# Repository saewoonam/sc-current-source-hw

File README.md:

# CAD file for supercables 8 channel current source

## Folder descriptions:
- 8ch_currentsource_jlc_v4:   KiCAD files of the elecronic circuit
- front_panel:  PCB design for the front panel of the enclosure
- back_panel:  PCB design for rthe back panel of the enclosure
- supercables-curernt-source-enclosure:  FreeCAD file and step files of the assembled box

## [Assembly Instructions](https://github.com/saewoonam/sc-current-source-hw/blob/main/Assembly_Instructions.md)

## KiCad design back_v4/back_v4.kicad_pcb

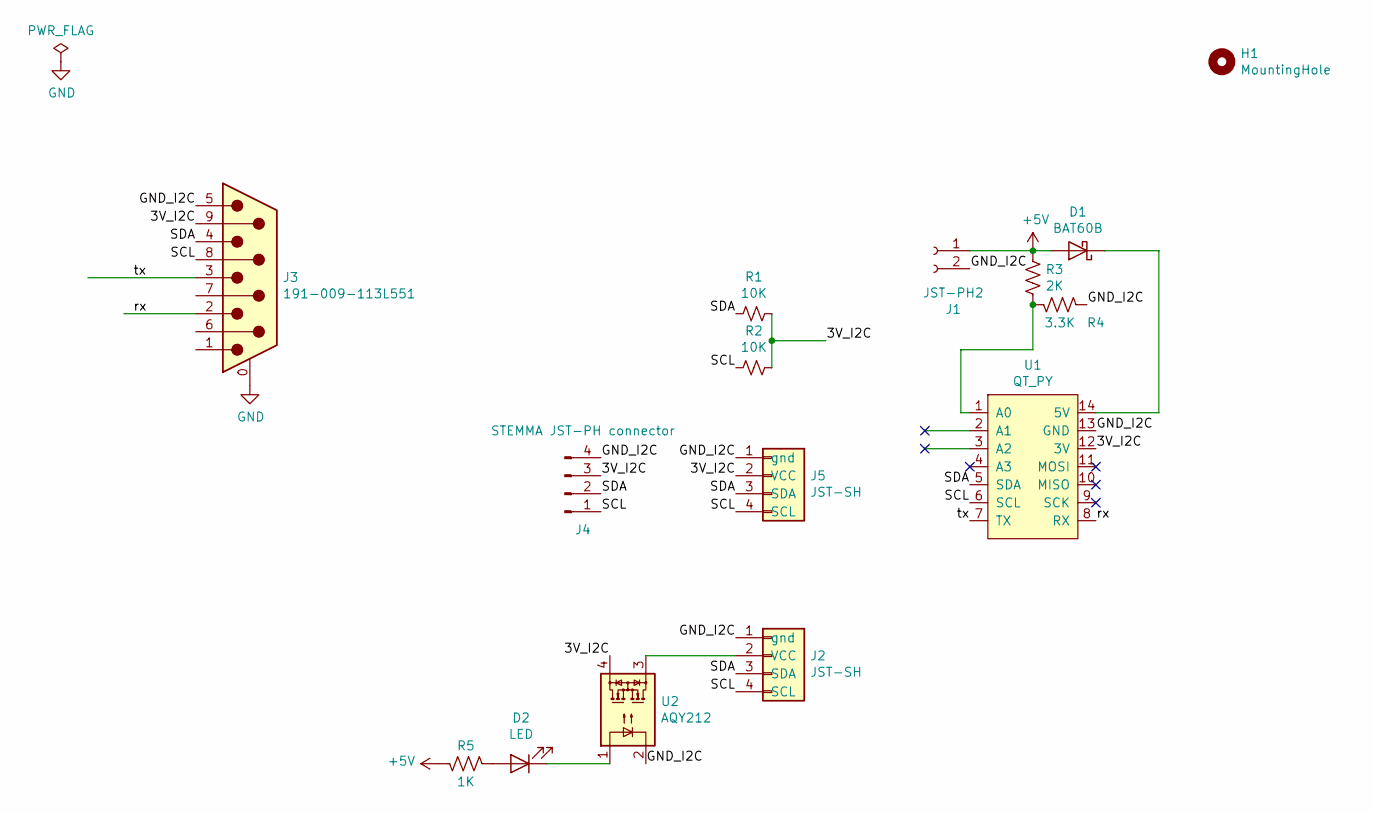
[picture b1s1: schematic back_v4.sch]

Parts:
D1: BAT60B; D_SOD-323; MPN BAT60B; LCSC C514095
D2: LED; LED_0603_1608Metric_Pad1.05x0.95mm_HandSolder; MPN KT-0603R; LCSC C2286
H1: MountingHole; MountingHole_8.4mm_PJ-066
J1: JST-PH2; JST_PH_B2B-PH-SM4-TB_1x02-1MP_P2.00mm_Vertical; MPN B2B-PH-SM4-TB(lf)(sn)
J2, J5: JST-SH; JST_SH_BM04B-SRSS-TB_1x04-1MP_P1.00mm_Vertical; MPN JST-SH-BM04B-SRSS-TB
J3: 191-009-113L551; DSUB-9_Male_Vertical_P2.77x2.84mm_MountingHoles; MPN 191-009-113L551
J4: STEMMA JST-PH connector; JST_PH_B4B-PH-SM4-TB_1x04-1MP_P2.00mm_Vertical; MPN B4B-PH-SM4-TB(lf)(sn)
R1: 10K; R_0603_1608Metric_Pad1.05x0.95mm_HandSolder; MPN 0603WAF1002T5E
R2: 10K; R_0603_1608Metric_Pad1.05x0.95mm_HandSolder; MPN 0603WAF1002T5E; LCSC C25804
R3: 2K; R_0603_1608Metric_Pad1.05x0.95mm_HandSolder; MPN 0603WAF2001T5E; LCSC C22975
R4: 3.3K; R_0603_1608Metric_Pad1.05x0.95mm_HandSolder; MPN 0603WAF3301T5E; LCSC C22978
R5: 1K; R_0603_1608Metric_Pad1.05x0.95mm_HandSolder; MPN 0603WAF1001T5E; LCSC C21190
U1: QT_PY; QT_PY_DIP-14_600_ELL
U2: AQY212; SO-4_4.4x4.3mm_P2.54mm; MPN AQY212GSZ; LCSC C129283

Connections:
+5V: D1.2 (A), J1.1, R3.1, R5.1
/3V_I2C: J3.9, J4.3, J5.2 (VCC), R1.1, R2.1, U1.12 (3V), U2.4
/GND_I2C: J1.2, J2.1 (gnd), J3.5, J4.4, J5.1 (gnd), R4.2, U1.13 (GND), U2.2
/SCL: J2.4 (SCL), J3.8, J4.1, J5.4 (SCL), R2.2, U1.6 (SCL)
/SDA: J2.3 (SDA), J3.4, J4.2, J5.3 (SDA), R1.2, U1.5 (SDA)
/rx: J3.2, U1.8 (RX)
/tx: J3.3, U1.7 (TX)
GND: J3.0 (PAD)
unnamed: D1.1 (K), U1.14 (5V)
unnamed: D2.1 (K), U2.1
unnamed: D2.2 (A), R5.2
unnamed: J2.2 (VCC), U2.3
unnamed: R3.2, R4.1, U1.1 (A0)

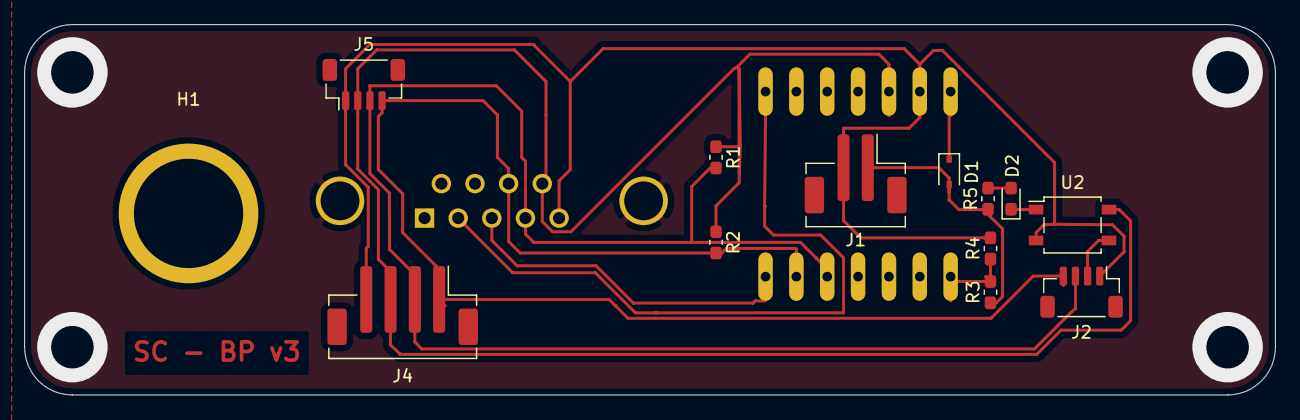
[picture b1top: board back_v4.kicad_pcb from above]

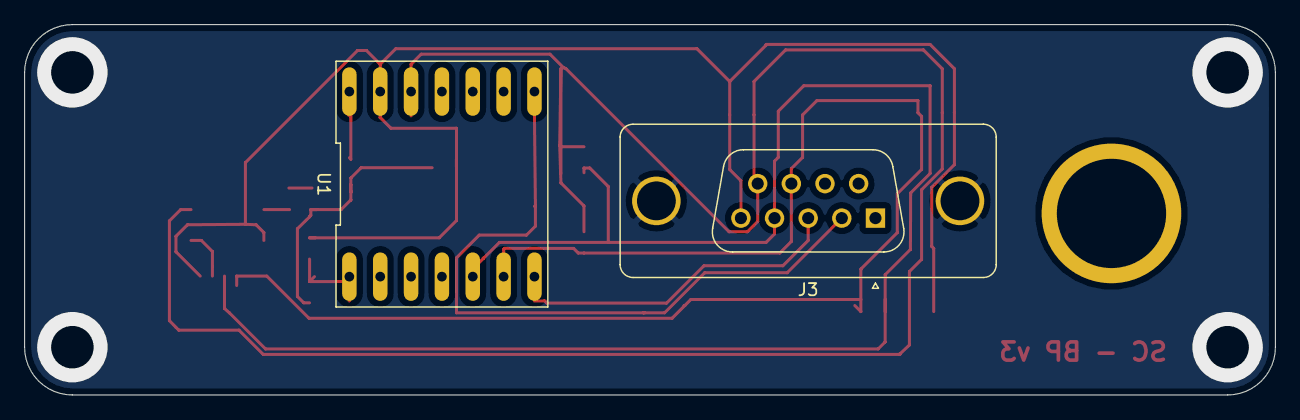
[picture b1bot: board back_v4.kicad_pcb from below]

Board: 2 copper layers, 103.0 x 30.5 mm, 15 parts (2 on the bottom side), 12 nets.

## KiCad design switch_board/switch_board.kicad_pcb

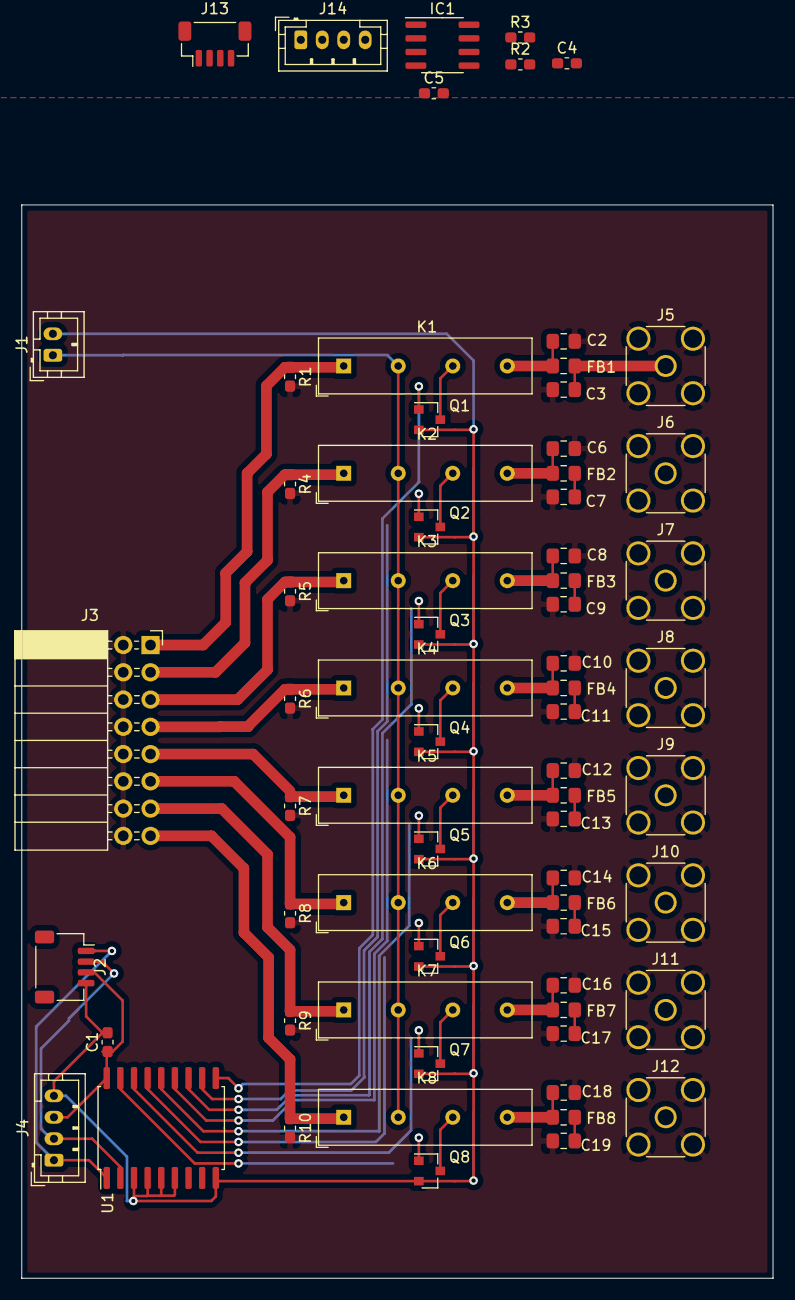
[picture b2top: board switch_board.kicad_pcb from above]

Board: 2 copper layers, 70.0 x 100.0 mm, 69 parts (0 on the bottom side), 52 nets.

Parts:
C1, C4, C5: 100nF; C_0603_1608Metric_Pad1.05x0.95mm_HandSolder
C2, C3, C6, C7, C8, C9, C10, C11, C12, C13, C14, C15, C16, C17, C18, C19: 100uF; C_0805_2012Metric_Pad1.15x1.40mm_HandSolder
FB1, FB2, FB3, FB4, FB5, FB6, FB7, FB8: 4.7uH; L_0805_2012Metric_Pad1.15x1.40mm_HandSolder
IC1: ISO1541DR; SOIC-8_3.9x4.9mm_P1.27mm
J1: Conn_01x02; JST_PH_B2B-PH-K_1x02_P2.00mm_Vertical
J2: Conn_01x04_i2c; JST_SH_SM04B-SRSS-TB_1x04-1MP_P1.00mm_Horizontal
J3: Conn_02x08_Odd_Even; PinSocket_2x08_P2.54mm_Horizontal
J4: Conn_01x04_i2c; JST_PH_B4B-PH-K_1x04_P2.00mm_Vertical
J5, J6, J7, J8, J9, J10, J11, J12: Conn_Coaxial; SMA_Amphenol_132134_Vertical
J13: Conn_01x04_i2c; JST_SH_BM04B-SRSS-TB_1x04-1MP_P1.00mm_Vertical
J14: B4B-PH-K; JST_PH_B4B-PH-K_1x04_P2.00mm_Vertical
K1, K2, K3, K4, K5, K6, K7, K8: SILxx-1Axx-71x; Relay_SPST_StandexMeder_SIL_Form1A
Q1, Q2, Q3, Q4, Q5, Q6, Q7, Q8: NUD3105LT1G; SOT-23
R1, R2, R3, R4, R5, R6, R7, R8, R9, R10: 10K; R_0603_1608Metric_Pad1.05x0.95mm_HandSolder
U1: MCP23008-E_SO; SOIC-18W_7.5x11.6mm_P1.27mm

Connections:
+5V: J1.1, K1.3, K2.3, K3.3, K4.3, K5.3, K6.3, K7.3, K8.3
/Sheet601B3DC5/out: C3.1, FB1.1, J5.1
/Sheet601B43CA/Vin: C4.1, IC1.1, J13.3, J14.3
/Sheet601B43CA/Vpower: C5.1, IC1.8, R2.1, R3.1
/Sheet601B43CA/scl: IC1.6, R3.2
/Sheet601B43CA/sda: IC1.7, R2.2
/in0: J3.1, K1.1, R1.1
/in1: J3.3, K2.1, R4.1
/in2: J3.5, K3.1, R5.1
/in3: J3.7, K4.1, R6.1
/in4: J3.9, K5.1, R7.1
/in5: J3.11, K6.1, R8.1
/in6: J3.13, K7.1, R9.1
/in7: J3.15, K8.1, R10.1
/s0: Q1.1, U1.10
/s1: Q2.1, U1.11
/s2: Q3.1, U1.12
/s3: Q4.1, U1.13
/s4: Q5.1, U1.14
/s5: Q6.1, U1.15
/s6: Q7.1, U1.16
/s7: Q8.1, U1.17
/scl: J2.1, J4.1, U1.1
/sda: J2.2, J4.2, U1.2
/sheet601BFE22/out: C7.1, FB2.1, J6.1
/sheet601C077A/out: C17.1, FB7.1, J11.1
/sheet601C077B/out: C19.1, FB8.1, J12.1
/sheet601C0132/out: C9.1, FB3.1, J7.1
/sheet601C0133/out: C11.1, FB4.1, J8.1
/sheet601C0778/out: C13.1, FB5.1, J9.1
/sheet601C0779/out: C15.1, FB6.1, J10.1
GND: C2.2, C3.2, C5.2, C6.2, C7.2, C8.2, C9.2, C10.2, C11.2, C12.2, C13.2, C14.2, C15.2, C16.2, C17.2, C18.2, C19.2, IC1.5, J3.2, J3.4, J3.6, J3.8, J3.10, J3.12, J3.14, J3.16, J5.2, J6.2, J7.2, J8.2, J9.2, J10.2, J11.2, J12.2, R1.2, R4.2, R5.2, R6.2, R7.2, R8.2, R9.2, R10.2
GNDD: C1.2, C4.2, IC1.4, J1.2, J2.4, J4.4, J13.4, J14.4, Q1.2, Q2.2, Q3.2, Q4.2, Q5.2, Q6.2, Q7.2, Q8.2, U1.3, U1.4, U1.5, U1.6, U1.9
unnamed: C2.1, FB1.2, K1.7
unnamed: C6.1, FB2.2, K2.7
unnamed: C8.1, FB3.2, K3.7
unnamed: C10.1, FB4.2, K4.7
unnamed: C12.1, FB5.2, K5.7
unnamed: C14.1, FB6.2, K6.7
unnamed: C16.1, FB7.2, K7.7
unnamed: C18.1, FB8.2, K8.7
unnamed: IC1.2, J13.2, J14.2
unnamed: IC1.3, J13.1, J14.1
unnamed: K1.5, Q1.3
unnamed: K2.5, Q2.3
unnamed: K3.5, Q3.3
unnamed: K4.5, Q4.3
unnamed: K5.5, Q5.3
unnamed: K6.5, Q6.3
unnamed: K7.5, Q7.3
unnamed: K8.5, Q8.3
VCC: C1.1, J2.3, J4.3, U1.18

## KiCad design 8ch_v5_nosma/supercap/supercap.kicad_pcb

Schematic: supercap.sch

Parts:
C5, C6: CP; C_Radial_D21.5mm_H8mm_P5.00mm; MPN DB-5R5D155T
C7: 100uF; C_1210_3225Metric_Pad1.42x2.65mm_HandSolder; MPN CL32A107MQVNNNE; LCSC C49066
D1, D2, D3, D4: BAT60A; D_SOD-323; MPN BAT60AE6327
D5: BAT60A; D_SOD-323; MPN BAT60AE6327; LCSC C117485
J1, J8, J9: JST_SH_Conn_01x04_i2c; JST_SH_BM04B-SRSS-TB_1x04-1MP_P1.00mm_Vertical
J2, J3, J4, J5, J7: Conn_01x02; JST_PH_B2B-PH-K_1x02_P2.00mm_Vertical; MPN B2B-PH-K-S(LF)(SN)
Q1, Q2: NUD3105LT1G; SOT-23; MPN NUD3105LT1G; LCSC C14894
Q3: BSS84; SOT-23; LCSC C8492
R1, R3: 15 ohm 2W / 33 ohm 1W; R_2512_6332Metric_Pad1.52x3.35mm_HandSolder; MPN CRM2512-FX-15R0ELF; LCSC C53728
R2, R6: 1K; R_0603_1608Metric_Pad1.05x0.95mm_HandSolder; MPN 0603WAF1001T5E; LCSC C21190
R4, R5, R8: 750; R_0603_1608Metric_Pad1.05x0.95mm_HandSolder; MPN 0603WAF7500T5E; LCSC C23241
R7: 10K; R_0603_1608Metric_Pad1.05x0.95mm_HandSolder; MPN 0603WAF1002T5E; LCSC C25804
U1, U2, U3: AQY212GSZ; SO-4_4.4x4.3mm_P2.54mm; MPN AQY212GSZ; LCSC C129283

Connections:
/5V: D3.2, J2.1, Q3.2, R1.1, R8.2
/-5V: D4.1, J7.2, R3.2
/-Vin: D2.2, D4.2, U2.3
/-Vout: J4.2, U2.4
/Vin: D1.1, D3.1, R4.1, R5.1, U3.4
/Vout: J3.1, J5.1, U3.3
GND: C5.2, C6.1, C7.1, J2.2, J3.2, J4.1, J5.2, J7.1, Q1.2, Q2.2, R6.2, R7.1, U1.2
unnamed: C5.1, D1.2, R1.2
unnamed: C6.2, D2.1, R3.1
unnamed: C7.2, Q1.1, Q2.1, R2.1, R7.2
unnamed: D5.1, R2.2
unnamed: D5.2, Q3.3
unnamed: J1.1, J8.1, J9.4
unnamed: J1.2, U1.4
unnamed: J1.3, J8.3, J9.2
unnamed: J1.4, J8.4, J9.1
unnamed: J8.2, J9.3, U1.3
unnamed: Q1.3, U3.2
unnamed: Q2.3, U2.2
unnamed: Q3.1, R6.1
unnamed: R4.2, U2.1
unnamed: R5.2, U3.1
unnamed: R8.1, U1.1

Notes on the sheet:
Power for current source
Power for microcontroller
Set time constant for switches to turn off when power is lost

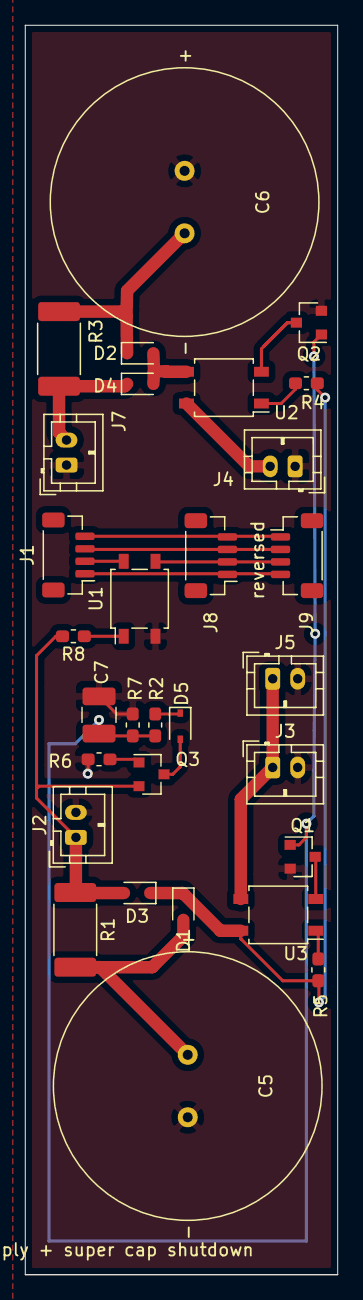
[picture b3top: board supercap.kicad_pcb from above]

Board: 2 copper layers, 25.0 x 100.0 mm, 30 parts (0 on the bottom side), 23 nets.

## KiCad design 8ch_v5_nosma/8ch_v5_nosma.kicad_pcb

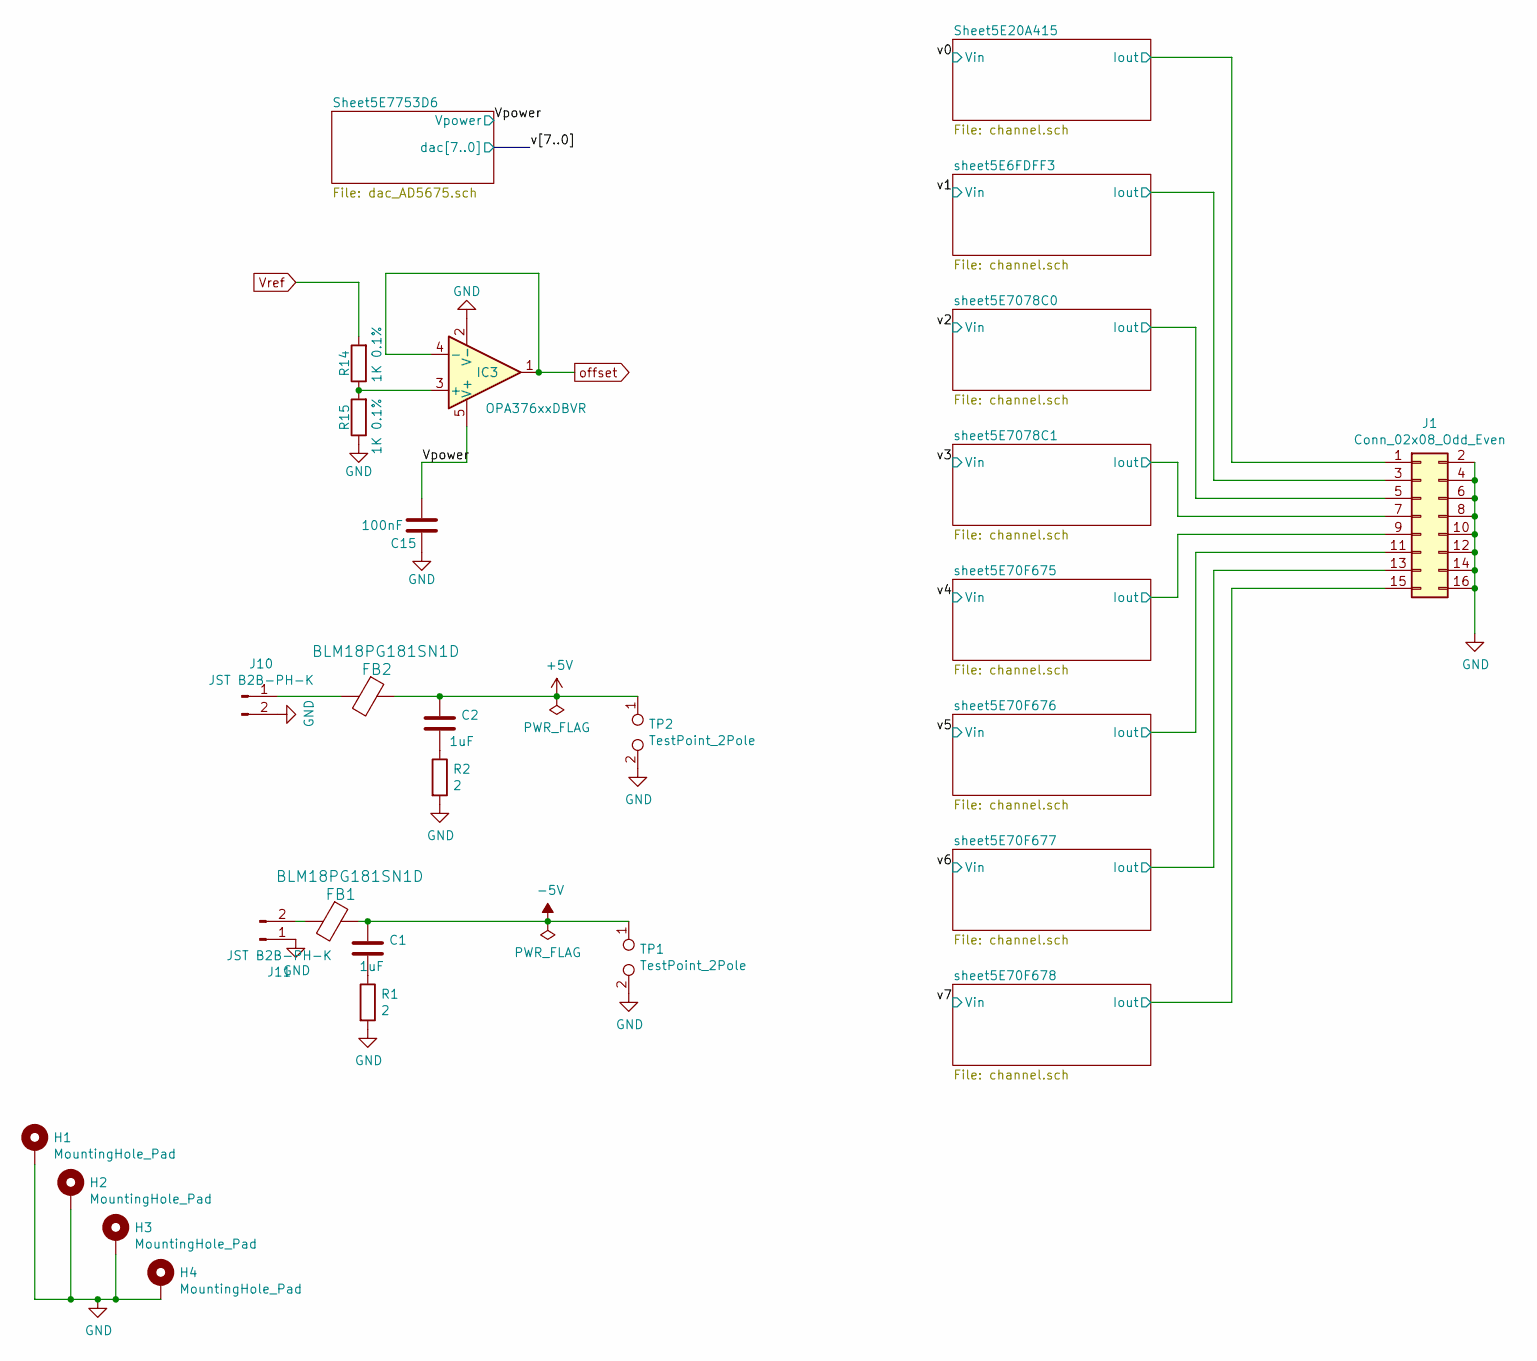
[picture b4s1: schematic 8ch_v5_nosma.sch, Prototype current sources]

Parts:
C1, C2: 1uF; C_0603_1608Metric_Pad1.05x0.95mm_HandSolder; MPN CL10B105KA8NNNC
C15: 100nF; C_0603_1608Metric_Pad1.05x0.95mm_HandSolder; MPN CC0603KPX7R7BB104; Digikey 490-1767-1-ND
FB1, FB2: BLM18PG181SN1D; L_0603_1608Metric_Pad1.05x0.95mm_HandSolder; MPN BLM18PG181SN1D
H1, H2, H3, H4: MountingHole_Pad; MountingHole_3.2mm_M3_Pad_Via
IC3: OPA376xxDBVR; SOT-23-5; MPN OPA376AIDBVR
J1: Conn_02x08_Odd_Even; PinHeader_2x08_P2.54mm_Horizontal; MPN PRPC008DBAN-M71RC
J10, J11: JST B2B-PH-K; JST_PH_B2B-PH-K_1x02_P2.00mm_Vertical; MPN B2B-PH-K-S(LF)(SN)
R1, R2: 2; R_0603_1608Metric_Pad1.05x0.95mm_HandSolder; MPN 0603WAF200KT5E
R14, R15: 1K 0.1%; R_0603_1608Metric_Pad1.05x0.95mm_HandSolder; MPN TC0325B1001T5E
TP1, TP2: TestPoint_2Pole; TestPoint_2Pads_Pitch2.54mm_Drill0.8mm

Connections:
+5V: C2.1, FB2.1, TP2.1; also elsewhere on the board
-5V: C1.1, FB1.1, TP1.1; also elsewhere on the board
/Sheet5E20A415/Iout: J1.1; also elsewhere on the board
/Vpower: C15.2, IC3.5 (V+); also elsewhere on the board
/sheet5E6FDFF3/Iout: J1.3; also elsewhere on the board
/sheet5E70F675/Iout: J1.9; also elsewhere on the board
/sheet5E70F676/Iout: J1.11; also elsewhere on the board
/sheet5E70F677/Iout: J1.13; also elsewhere on the board
/sheet5E70F678/Iout: J1.15; also elsewhere on the board
/sheet5E7078C0/Iout: J1.5; also elsewhere on the board
/sheet5E7078C1/Iout: J1.7; also elsewhere on the board
GND: C15.1, H1.1, H2.1, H3.1, H4.1, IC3.2 (V-), J1.2, J1.4, J1.6, J1.8, J1.10, J1.12, J1.14, J1.16, J10.2, J11.1, R1.2, R2.2, R15.1, TP1.2, TP2.2; also elsewhere on the board
unnamed: C1.2, R1.1
unnamed: C2.2, R2.1
unnamed: FB1.2, J11.2
unnamed: FB2.2, J10.1
unnamed: IC3.3 (+), R14.1, R15.2
Vref: R14.2; also elsewhere on the board
offset: IC3.1, IC3.4 (-); also elsewhere on the board

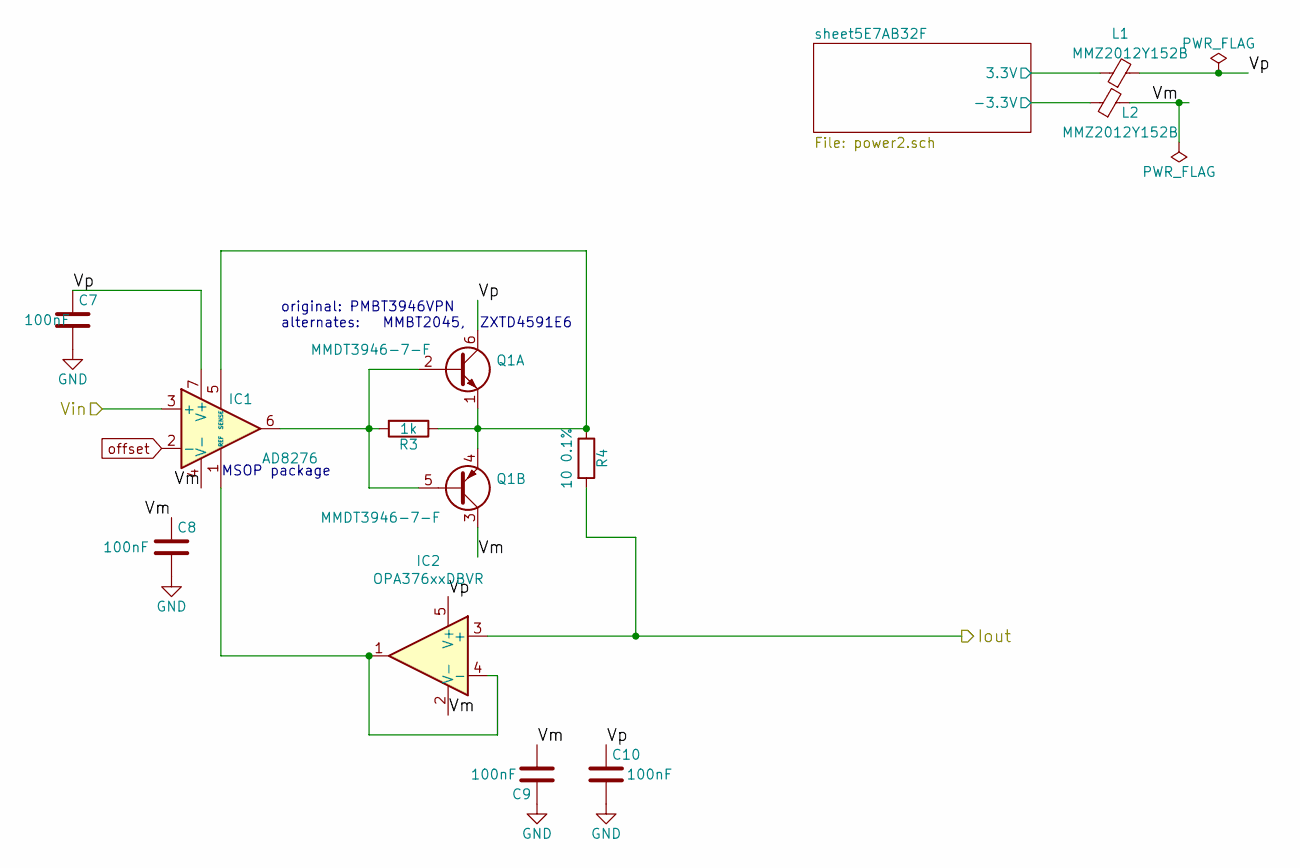
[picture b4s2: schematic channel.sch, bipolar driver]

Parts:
C7, C8, C9, C10: 100nF; C_0603_1608Metric_Pad1.05x0.95mm_HandSolder; Part GRM31C5C1E104JA01L; Digikey 490-1767-1-ND
IC1: AD8276; MSOP-8_3x3mm_P0.65mm; MPN-backup INA132UA/2K5; LCSC C38199
IC2: OPA376xxDBVR; SOT-23-5; MPN OPA376AIDBVR; LCSC C42314
L1, L2: MMZ2012Y152B; L_0805_2012Metric_Pad1.15x1.40mm_HandSolder; MPN MMZ2012Y152BTD25
Q1: MMDT3946-7-F; SOT-363_SC-70-6; MPN MMDT3946-7-F; LCSC C151354
R3: 1k; R_0603_1608Metric_Pad1.05x0.95mm_HandSolder; MPN RC0603FR-071KL
R4: 10 0.1%; R_0805_2012Metric; MPN TC0525B100JT5E

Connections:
/Sheet5E20A415/Iout: IC2.3 (+), R4.2; also elsewhere on the board
/Sheet5E20A415/Vm: C8.1, C9.2, IC1.4 (V-), IC2.2 (V-), L2.2, Q1.3 (C2)
/Sheet5E20A415/Vp: C7.1, C10.1, IC1.7 (V+), IC2.5 (V+), L1.2, Q1.6 (C1)
/Sheet5E20A415/sheet5E7AB32F/3.3V: L1.1; also elsewhere on the board
/Sheet5E20A415/sheet5E7AB32F/-3.3V: L2.1; also elsewhere on the board
/v0: IC1.3 (+); also elsewhere on the board
GND: C7.2, C8.2, C9.1, C10.2; also elsewhere on the board
unnamed: IC1.1 (REF), IC2.1, IC2.4 (-)
unnamed: IC1.5 (SENSE), Q1.1 (E1), Q1.4 (E2), R3.1, R4.1
unnamed: IC1.6, Q1.2 (B1), Q1.5 (B2), R3.2
offset: IC1.2 (-); also elsewhere on the board

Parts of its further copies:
C11, C12, C16, C17, C18, C19, C20, C21, C22, C23, C24, C25, C26, C27, C28, C29, C30, C31, C32, C33, C34, C35, C36, C37, C38, C39, C40, C41: 100nF; C_0603_1608Metric_Pad1.05x0.95mm_HandSolder; Part GRM31C5C1E104JA01L; Digikey 490-1767-1-ND
IC4, IC6, IC8, IC10, IC12, IC14, IC16: AD8276; MSOP-8_3x3mm_P0.65mm; MPN-backup INA132UA/2K5; LCSC C38199
IC5, IC7, IC9, IC11, IC13, IC15, IC17: OPA376xxDBVR; SOT-23-5; MPN OPA376AIDBVR; LCSC C42314
L3, L4, L5, L6, L7, L8, L9, L10, L11, L12, L13, L14, L15, L16: MMZ2012Y152B; L_0805_2012Metric_Pad1.15x1.40mm_HandSolder; MPN MMZ2012Y152BTD25
Q2, Q3, Q4, Q5, Q6, Q7, Q8: MMDT3946-7-F; SOT-363_SC-70-6; MPN MMDT3946-7-F; LCSC C151354
R6, R9, R16, R19, R22, R25, R28: 1k; R_0603_1608Metric_Pad1.05x0.95mm_HandSolder; MPN RC0603FR-071KL
R7, R10, R17, R20, R23, R26, R29: 10 0.1%; R_0805_2012Metric; MPN TC0525B100JT5E

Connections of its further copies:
/sheet5E6FDFF3/Iout: IC5.3 (+), R7.2; also elsewhere on the board
/sheet5E6FDFF3/Vm: C12.1, C16.2, IC4.4 (V-), IC5.2 (V-), L4.2, Q2.3 (C2)
/sheet5E6FDFF3/Vp: C11.1, C17.1, IC4.7 (V+), IC5.5 (V+), L3.2, Q2.6 (C1)
/sheet5E6FDFF3/sheet5E7AB32F/3.3V: L3.1; also elsewhere on the board
/sheet5E6FDFF3/sheet5E7AB32F/-3.3V: L4.1; also elsewhere on the board
/sheet5E70F675/Iout: IC11.3 (+), R20.2; also elsewhere on the board
/sheet5E70F675/Vm: C27.1, C28.2, IC10.4 (V-), IC11.2 (V-), L10.2, Q5.3 (C2)
/sheet5E70F675/Vp: C26.1, C29.1, IC10.7 (V+), IC11.5 (V+), L9.2, Q5.6 (C1)
/sheet5E70F675/sheet5E7AB32F/3.3V: L9.1; also elsewhere on the board
/sheet5E70F675/sheet5E7AB32F/-3.3V: L10.1; also elsewhere on the board
/sheet5E70F676/Iout: IC13.3 (+), R23.2; also elsewhere on the board
/sheet5E70F676/Vm: C31.1, C32.2, IC12.4 (V-), IC13.2 (V-), L12.2, Q6.3 (C2)
/sheet5E70F676/Vp: C30.1, C33.1, IC12.7 (V+), IC13.5 (V+), L11.2, Q6.6 (C1)
/sheet5E70F676/sheet5E7AB32F/3.3V: L11.1; also elsewhere on the board
/sheet5E70F676/sheet5E7AB32F/-3.3V: L12.1; also elsewhere on the board
/sheet5E70F677/Iout: IC15.3 (+), R26.2; also elsewhere on the board
/sheet5E70F677/Vm: C35.1, C36.2, IC14.4 (V-), IC15.2 (V-), L14.2, Q7.3 (C2)
/sheet5E70F677/Vp: C34.1, C37.1, IC14.7 (V+), IC15.5 (V+), L13.2, Q7.6 (C1)
/sheet5E70F677/sheet5E7AB32F/3.3V: L13.1; also elsewhere on the board
/sheet5E70F677/sheet5E7AB32F/-3.3V: L14.1; also elsewhere on the board
/sheet5E70F678/Iout: IC17.3 (+), R29.2; also elsewhere on the board
/sheet5E70F678/Vm: C39.1, C40.2, IC16.4 (V-), IC17.2 (V-), L16.2, Q8.3 (C2)
/sheet5E70F678/Vp: C38.1, C41.1, IC16.7 (V+), IC17.5 (V+), L15.2, Q8.6 (C1)
/sheet5E70F678/sheet5E7AB32F/3.3V: L15.1; also elsewhere on the board
/sheet5E70F678/sheet5E7AB32F/-3.3V: L16.1; also elsewhere on the board
/sheet5E7078C0/Iout: IC7.3 (+), R10.2; also elsewhere on the board
/sheet5E7078C0/Vm: C19.1, C20.2, IC6.4 (V-), IC7.2 (V-), L6.2, Q3.3 (C2)
/sheet5E7078C0/Vp: C18.1, C21.1, IC6.7 (V+), IC7.5 (V+), L5.2, Q3.6 (C1)
/sheet5E7078C0/sheet5E7AB32F/3.3V: L5.1; also elsewhere on the board
/sheet5E7078C0/sheet5E7AB32F/-3.3V: L6.1; also elsewhere on the board
/sheet5E7078C1/Iout: IC9.3 (+), R17.2; also elsewhere on the board
/sheet5E7078C1/Vm: C23.1, C24.2, IC8.4 (V-), IC9.2 (V-), L8.2, Q4.3 (C2)
/sheet5E7078C1/Vp: C22.1, C25.1, IC8.7 (V+), IC9.5 (V+), L7.2, Q4.6 (C1)
/sheet5E7078C1/sheet5E7AB32F/3.3V: L7.1; also elsewhere on the board
/sheet5E7078C1/sheet5E7AB32F/-3.3V: L8.1; also elsewhere on the board
/v1: IC4.3 (+); also elsewhere on the board
/v2: IC6.3 (+); also elsewhere on the board
/v3: IC8.3 (+); also elsewhere on the board
/v4: IC10.3 (+); also elsewhere on the board
/v5: IC12.3 (+); also elsewhere on the board
/v6: IC14.3 (+); also elsewhere on the board
/v7: IC16.3 (+); also elsewhere on the board
GND: C11.2, C12.2, C16.1, C17.2, C18.2, C19.2, C20.1, C21.2, C22.2, C23.2, C24.1, C25.2, C26.2, C27.2, C28.1, C29.2, C30.2, C31.2, C32.1, C33.2, C34.2, C35.2, C36.1, C37.2, C38.2, C39.2, C40.1, C41.2; also elsewhere on the board
unnamed: IC4.1 (REF), IC5.1, IC5.4 (-)
unnamed: IC4.5 (SENSE), Q2.1 (E1), Q2.4 (E2), R6.1, R7.1
unnamed: IC4.6, Q2.2 (B1), Q2.5 (B2), R6.2
unnamed: IC6.1 (REF), IC7.1, IC7.4 (-)
unnamed: IC6.5 (SENSE), Q3.1 (E1), Q3.4 (E2), R9.1, R10.1
unnamed: IC6.6, Q3.2 (B1), Q3.5 (B2), R9.2
unnamed: IC8.1 (REF), IC9.1, IC9.4 (-)
unnamed: IC8.5 (SENSE), Q4.1 (E1), Q4.4 (E2), R16.1, R17.1
unnamed: IC8.6, Q4.2 (B1), Q4.5 (B2), R16.2
unnamed: IC10.1 (REF), IC11.1, IC11.4 (-)
unnamed: IC10.5 (SENSE), Q5.1 (E1), Q5.4 (E2), R19.1, R20.1
unnamed: IC10.6, Q5.2 (B1), Q5.5 (B2), R19.2
unnamed: IC12.1 (REF), IC13.1, IC13.4 (-)
unnamed: IC12.5 (SENSE), Q6.1 (E1), Q6.4 (E2), R22.1, R23.1
unnamed: IC12.6, Q6.2 (B1), Q6.5 (B2), R22.2
unnamed: IC14.1 (REF), IC15.1, IC15.4 (-)
unnamed: IC14.5 (SENSE), Q7.1 (E1), Q7.4 (E2), R25.1, R26.1
unnamed: IC14.6, Q7.2 (B1), Q7.5 (B2), R25.2
unnamed: IC16.1 (REF), IC17.1, IC17.4 (-)
unnamed: IC16.5 (SENSE), Q8.1 (E1), Q8.4 (E2), R28.1, R29.1
unnamed: IC16.6, Q8.2 (B1), Q8.5 (B2), R28.2
offset: IC4.2 (-), IC6.2 (-), IC8.2 (-), IC10.2 (-), IC12.2 (-), IC14.2 (-), IC16.2 (-); also elsewhere on the board

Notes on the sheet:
original: PMBT3946VPN alternates: MMBT2045, ZXTD4591E6
MSOP package

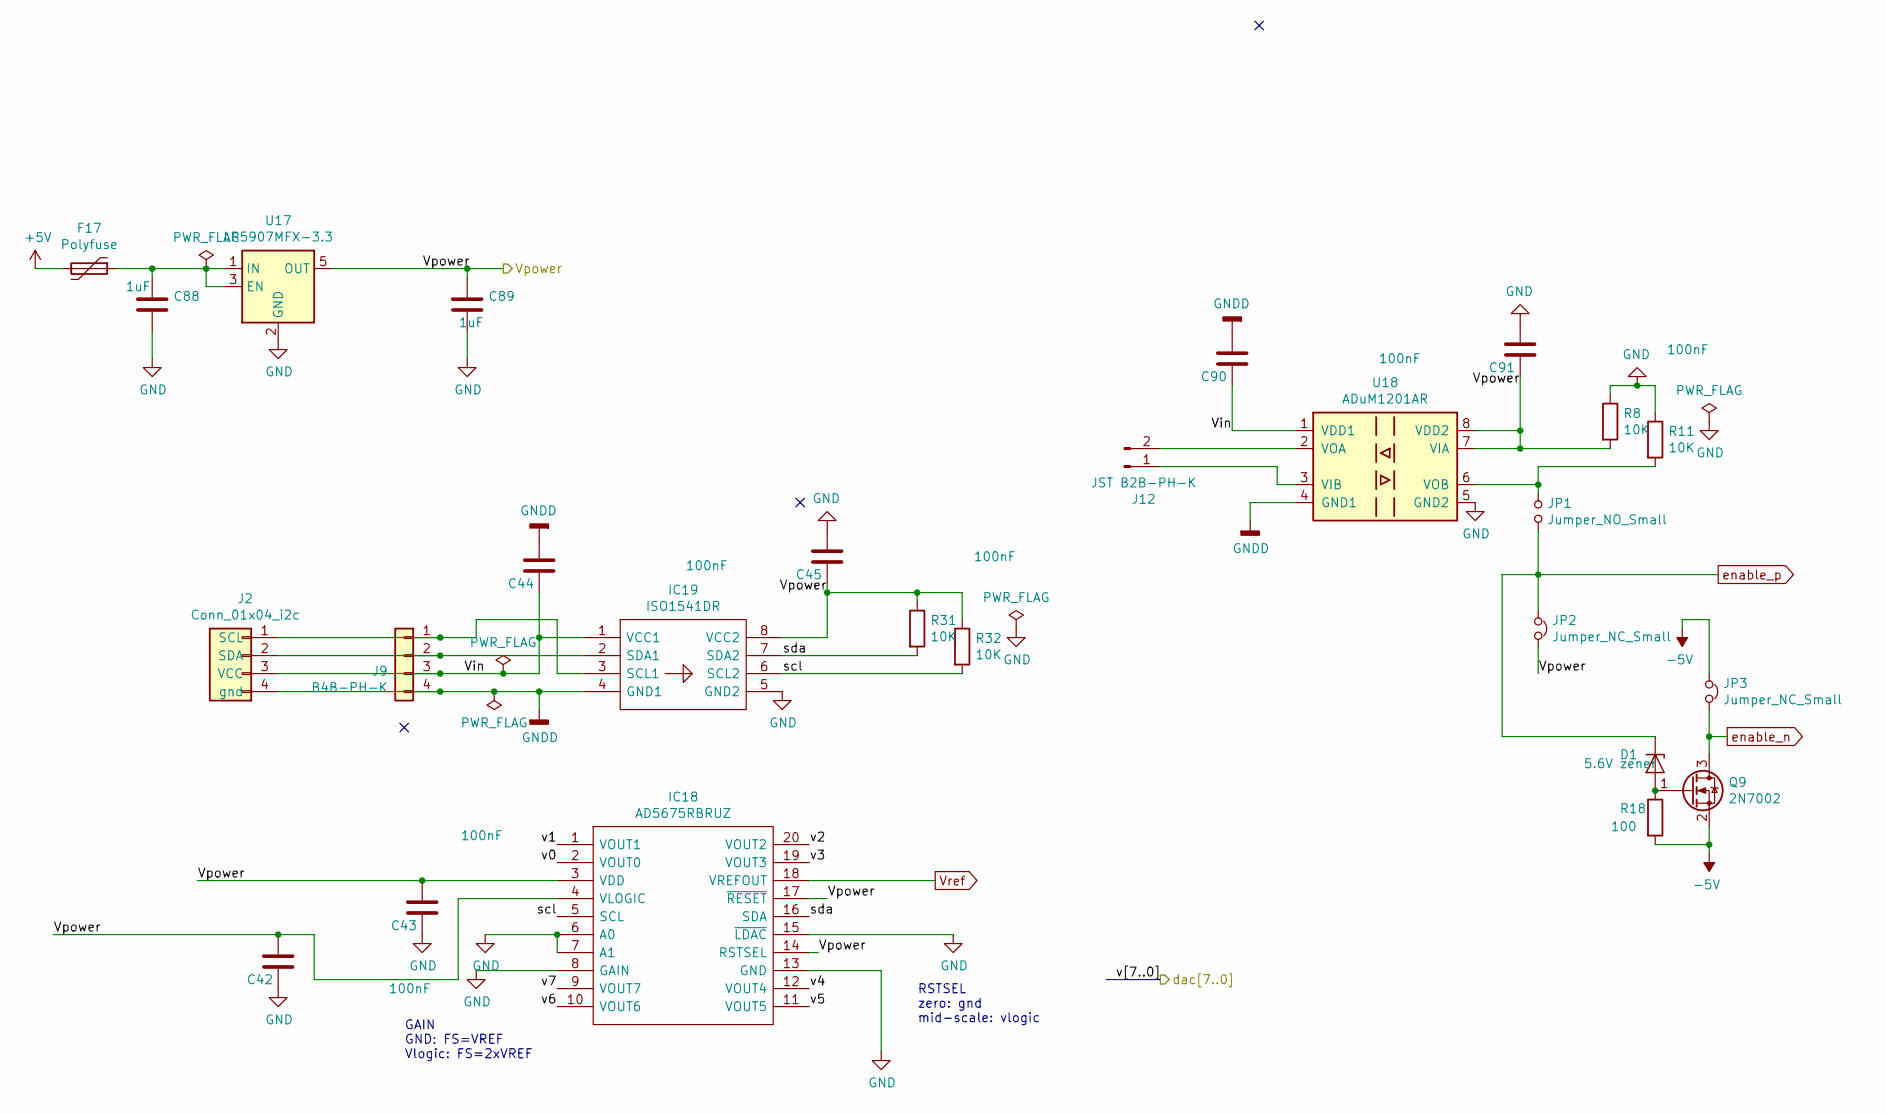
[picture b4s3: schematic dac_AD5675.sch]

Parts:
C42, C43, C44, C45, C90, C91: 100nF; C_0603_1608Metric_Pad1.05x0.95mm_HandSolder; Part CC0603KRX7R9BB104; Digikey 490-1767-1-ND
C88, C89: 1uF; C_0603_1608Metric_Pad1.05x0.95mm_HandSolder; MPN CL10B105KA8NNNC
D1: 5.6V zener; D_SOD-323; MPN BZT52C5V6S; LCSC C266579
F17: Polyfuse; Fuse_0603_1608Metric_Pad1.05x0.95mm_HandSolder; MPN TLC-FSMD020
IC18: AD5675RBRUZ; TSSOP-20_4.4x6.5mm_P0.65mm; MPN AD5675RBRUZ
IC19: ISO1541DR; SOIC-8_3.9x4.9mm_P1.27mm; MPN ISO1541DR
J2: Conn_01x04_i2c; JST_SH_BM04B-SRSS-TB_1x04-1MP_P1.00mm_Vertical; MPN JST_SH_BM04B-SRSS-TB
J9: B4B-PH-K; JST_PH_B4B-PH-K_1x04_P2.00mm_Vertical; MPN B4B-PH-K-S(LF)(SN)
J12: JST B2B-PH-K; JST_PH_B2B-PH-K_1x02_P2.00mm_Vertical; MPN B2B-PH-K-S(LF)(SN)
JP1: Jumper_NO_Small; SolderJumper-2_P1.3mm_Open_Pad1.0x1.5mm
JP2, JP3: Jumper_NC_Small; SolderJumper-2_P1.3mm_Bridged_Pad1.0x1.5mm
Q9: 2N7002; SOT-23; MPN 2N7002; LCSC C8545
R8, R11, R31, R32: 10K; R_0603_1608Metric_Pad1.05x0.95mm_HandSolder; MPN 0603WAF1002T5E
R18: 100; R_0603_1608Metric_Pad1.05x0.95mm_HandSolder; MPN 0603WAF1000T5E; LCSC C22775
U17: LP5907MFX-3.3; SOT-23-5; MPN LP5907MFX-3.3
U18: ADuM1201AR; SOIC-8_3.9x4.9mm_P1.27mm; MPN ADUM1201ARZ

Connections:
+5V: F17.2; also elsewhere on the board
-5V: JP3.1, Q9.2 (S), R18.2; also elsewhere on the board
/Sheet5E7753D6/Vin: C44.1, C90.1, IC19.1 (VCC1), J2.3 (VCC), J9.3, U18.1 (VDD1)
/Sheet5E7753D6/scl: IC18.5 (SCL), IC19.6 (SCL2), R32.2
/Sheet5E7753D6/sda: IC18.16 (SDA), IC19.7 (SDA2), R31.2
/Vpower: C42.2, C43.2, C45.1, C89.1, C91.1, IC18.3 (VDD), IC18.4 (VLOGIC), IC18.14 (RSTSEL), IC18.17 (~RESET), IC19.8 (VCC2), JP2.2, R8.2, R31.1, R32.1, U17.5 (OUT), U18.7 (VIA), U18.8 (VDD2); also elsewhere on the board
/v0: IC18.2 (VOUT0); also elsewhere on the board
/v1: IC18.1 (VOUT1); also elsewhere on the board
/v2: IC18.20 (VOUT2); also elsewhere on the board
/v3: IC18.19 (VOUT3); also elsewhere on the board
/v4: IC18.12 (VOUT4); also elsewhere on the board
/v5: IC18.11 (VOUT5); also elsewhere on the board
/v6: IC18.10 (VOUT6); also elsewhere on the board
/v7: IC18.9 (VOUT7); also elsewhere on the board
GND: C42.1, C43.1, C45.2, C88.2, C89.2, C91.2, IC18.6 (A0), IC18.7 (A1), IC18.8 (GAIN), IC18.13 (GND), IC18.15 (~LDAC), IC19.5 (GND2), R8.1, R11.1, U17.2 (GND), U18.5 (GND2); also elsewhere on the board
GNDD: C44.2, C90.2, IC19.4 (GND1), J2.4 (gnd), J9.4, U18.4 (GND1)
unnamed: C88.1, F17.1, U17.1 (IN), U17.3 (EN)
unnamed: D1.2 (A), Q9.1 (G), R18.1
unnamed: IC19.2 (SDA1), J2.2 (SDA), J9.2
unnamed: IC19.3 (SCL1), J2.1 (SCL), J9.1
unnamed: J12.1, U18.3 (VIB)
unnamed: J12.2, U18.2 (VOA)
unnamed: JP1.1, R11.2, U18.6 (VOB)
Vref: IC18.18 (VREFOUT); also elsewhere on the board
enable_n: JP3.2, Q9.3 (D); also elsewhere on the board
enable_p: D1.1 (K), JP1.2, JP2.1; also elsewhere on the board

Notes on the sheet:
GAIN GND: FS=VREF Vlogic: FS=2xVREF
RSTSEL zero: gnd mid-scale: vlogic
